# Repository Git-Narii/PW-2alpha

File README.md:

# PW-2alpha
電源基板
PW-2から降圧部分を取り除いた物  
電源用に24V,信号用に5Vを扱う  
12V非対応  
現時点で改良予定

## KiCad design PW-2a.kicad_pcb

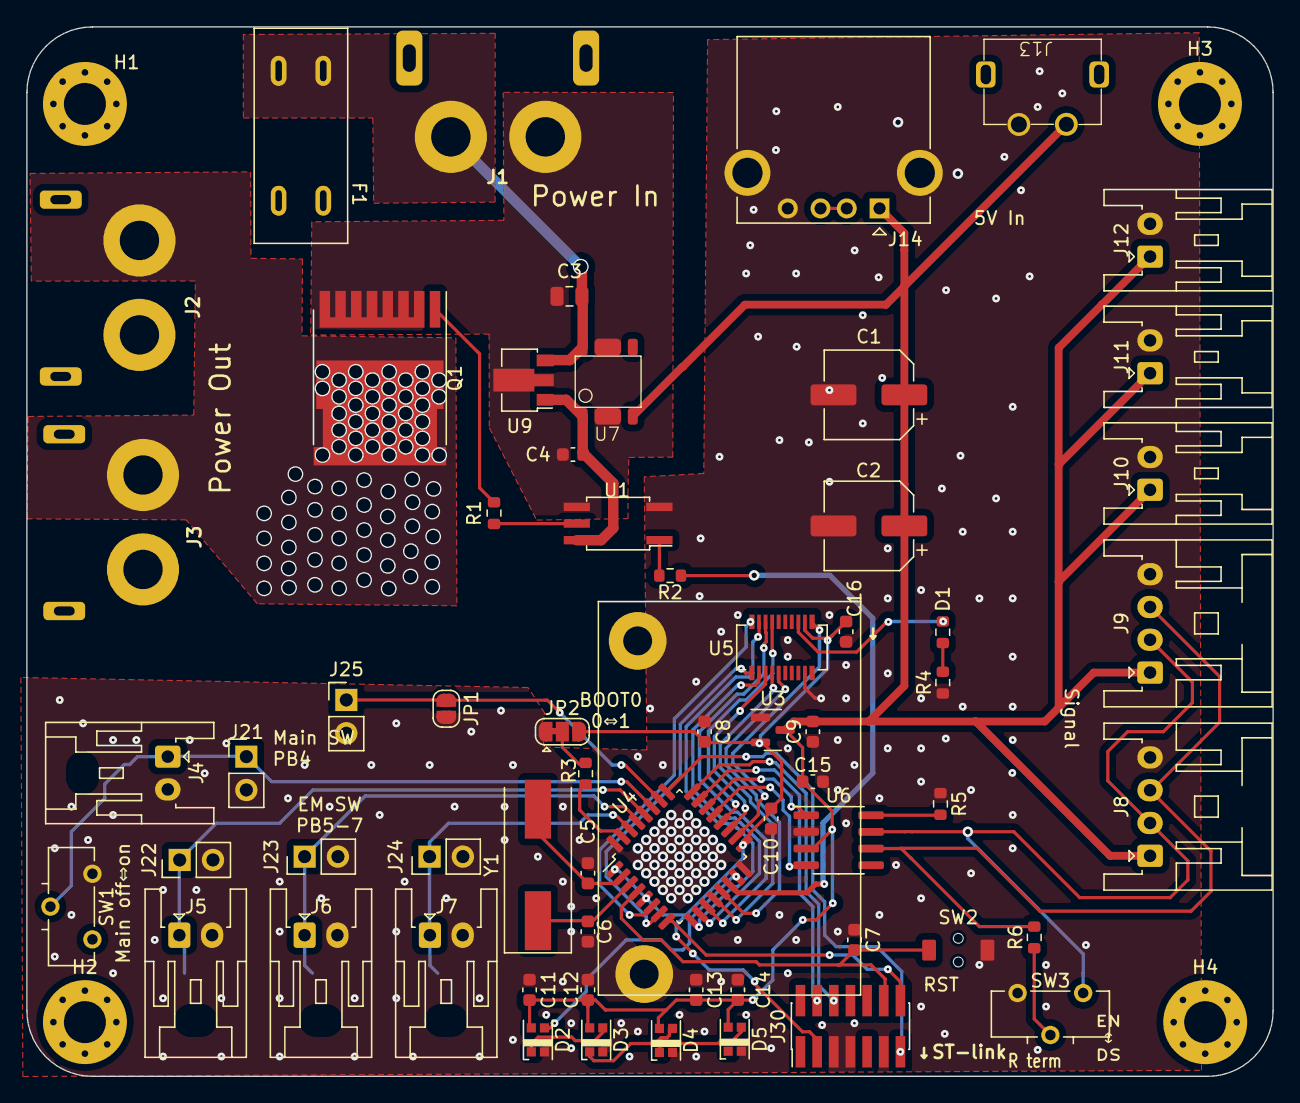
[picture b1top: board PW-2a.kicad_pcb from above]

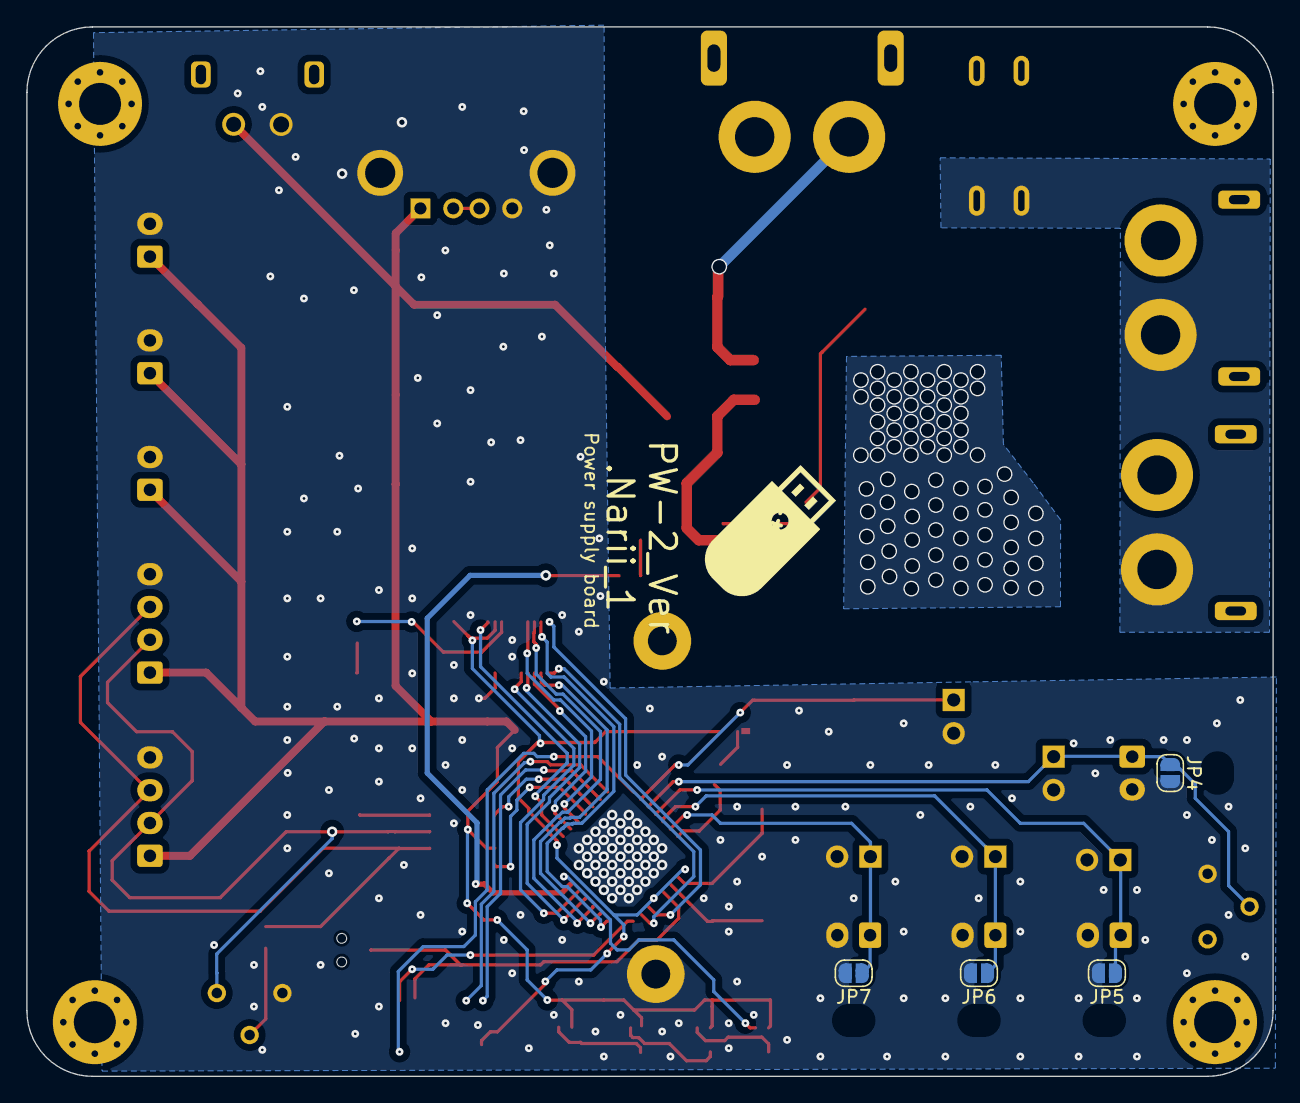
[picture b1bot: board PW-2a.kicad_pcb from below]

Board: 2 copper layers, 95.0 x 80.0 mm, 70 parts (4 on the bottom side), 49 nets.

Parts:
C1, C2: 33u; CP_Elec_6.3x7.7
C3: 330n; C_0805_2012Metric
C4, C7, C10, C11, C12, C13, C14, C15, C16: 100n; C_0603_1608Metric
C5, C6: 22p; C_0603_1608Metric
C8, C9: 1u; C_0603_1608Metric
D1: LED; R_0603_1608Metric
D2, D3, D4, D5: WS2812C; LED_2020Metric_WS2812C_2.0x2.0mm_P1.0mm
F1: Fuse; Fuseholder_Keystone_3568
H1, H2, H3, H4: MountingHole; MountingHole_3.2mm_M3_Pad_Via
J1, J2, J3: XT60
J4, J5, J6, J7, J10, J11, J12: Conn_01x02_Female; JST_XA_S02B-XASK-1_1x02_P2.50mm_Horizontal
J8, J9: Conn_01x04_Female; JST_XA_S04B-XASK-1_1x04_P2.50mm_Horizontal
J13: USB_C PowerOnly
J14: USB_A; USB_A_CONNFLY_DS1095-WNR0
J21, J22, J23, J24, J25: Conn_01x02_Male; PinHeader_1x02_P2.54mm_Vertical
J30: Conn_02x07_Odd_Even; PinHeader_2x07_P1.27mm_Vertical_SMD
JP1, JP4, JP5, JP6, JP7: SolderJumper_2_Open; SolderJumper-2_P1.3mm_Open_RoundedPad1.0x1.5mm
JP2: SolderJumper_3_Bridged12; SolderJumper-3_P1.3mm_Bridged12_RoundedPad1.0x1.5mm
Q1: IPT007N06N; Infineon_PG-HSOF-8-1
R1: 10; R_0603_1608Metric
R2: 330; R_0603_1608Metric
R3, R4, R5: 10k; R_0603_1608Metric
R6: 120; R_0603_1608Metric
SW1, SW3: SW_SPDT; IS-1245T-G
SW2: SW_Push; TVAF06-A020B-R
U1: TLP152; SO-6_5pin_4.4x3.6mm_P1.27mm
U3: MCP1700-3302E_SOT23; SOT-23
U4: STM32F303K8Tx; LQFP-32_7x7mm_P0.8mm
U5: IM920s
U6: MCP2551-I-SN; SOIC-8_3.9x4.9mm_P1.27mm
U7: S-1142DC0l-E6T1U; S-1142DC0I-E6T1U
U9: L78L33_SOT89; SOT-89-3
Y1: 16MHz; Crystal_SMD_HC49-SD

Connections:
+3V3: C8.2, C10.2, C16.2, J30.3, JP2.3 (B), U3.2 (VO), U4.1 (VDD), U4.5 (VDDA), U4.17 (VDD), U5.17 (VCC)
+5V: C1.1, C2.1, C9.2, C11.2, C12.2, C13.2, C14.2, C15.2, D2.4 (VDD), D3.4 (VDD), D4.4 (VDD), D5.4 (VDD), J8.1, J9.1, J10.1, J11.1, J12.1, J13.3 (VBUS), J14.1 (VBUS), U3.3 (VI), U6.3 (VDD), U7.3 (ON/OFF)
+12P: C4.2, U1.6, U7.1 (VOUT), U9.1 (OUT)
+BATT: C3.1, F1.1, J1.2, U7.6 (VIN), U9.3 (IN)
/CANH: J8.2, J9.2, SW3.3 (C), U6.7 (CANH)
/CANL: J8.3, J9.3, R6.2, U6.6 (CANL)
/CAN_RX: U4.21 (PA11), U6.4 (RXD)
/CAN_TX: U4.22 (PA12), U6.1 (TXD)
/IM920_IO1: U4.6 (PA0), U5.1 (IO1/BUSY)
/IM920_IO2: U4.7 (PA1), U5.2 (IO2)
/IM920_IO3: U4.9 (PA3), U5.3 (IO3/XMIT)
/IM920_IO4: U4.10 (PA4), U5.4 (IO4/SLEEP)
/IM920_IO5: U4.11 (PA5), U5.5 (IO5)
/IM920_IO6: U4.19 (PA9), U5.6 (IO6/RxD)
/IM920_IO7: U4.20 (PA10), U5.7 (IO7/TxD)
/IM920_IO8: U4.12 (PA6), U5.8 (IO8)
/IM920_IO10: U4.13 (PA7), U5.10 (IO10)
/IM920_RESET: U4.18 (PA8), U5.19 (RESET)
/NRST: C7.2, J30.12, SW2.2, U4.4 (NRST)
/NeoPixel: D2.3 (DIN), U4.15 (PB1)
/SWCLK: J30.6, U4.24 (PA14)
/SWDIO: J30.4, U4.23 (PA13)
/SW_IN1: J4.1, J21.1, JP4.1 (A), SW1.2 (B), U4.27 (PB4)
/SW_IN2: J5.1, J22.1, JP5.1 (A), U4.28 (PB5)
/SW_IN3: J6.1, J23.1, JP6.1 (A), U4.29 (PB6)
/SW_IN4: J7.1, J24.1, JP7.1 (A), U4.30 (PB7)
/VCP_RX: J30.13, U4.25 (PA15)
/VCP_TX: J30.14, U4.8 (PA2)
/Vout+: F1.2, J2.2, J3.2
/Vout-: J2.1, J3.1, Q1.3 (D)
/breaker_signal: R2.2, U4.14 (PB0)
/disable_remote_kill: J25.1, JP1.1 (A), U4.26 (PB3)
/main_breaker_gate: R1.2, U1.5
GND: C1.2, C2.2, C5.1, C6.1, C7.1, C8.1, C9.1, C10.1, C11.1, C12.1, C13.1, C14.1, C15.1, C16.1, D2.2 (VSS), D3.2 (VSS), D4.2 (VSS), D5.2 (VSS), J4.2, J5.2, J6.2, J7.2, J8.4, J9.4, J10.2, J11.2, J12.2, J13.4 (GND), J14.4 (GND), J14.5 (Shield), J21.2, J22.2, J23.2, J24.2, J25.2, J30.5, J30.7, J30.11, JP1.2 (B), JP2.1 (A), JP4.2 (B), JP5.2 (B), JP6.2 (B), JP7.2 (B), R4.1, R5.1, SW1.1 (A), SW2.1, SW3.1 (A), U1.3, U3.1 (GND), U4.16 (VSS), U4.32 (VSS), U5.18 (GND), U6.2 (VSS)
GNDPWR: C3.2, C4.1, J1.1, Q1.2 (S), U1.4, U7.2 (GND), U7.5 (GND), U9.2 (GND)
unnamed: D1.2 (A), U5.15 (STATUS)
unnamed: D1.1 (K), R4.2
unnamed: D2.1 (DOUT), D3.3 (DIN)
unnamed: D3.1 (DOUT), D4.3 (DIN)
unnamed: D4.1 (DOUT), D5.3 (DIN)
unnamed: J14.2 (D-), J14.3 (D+)
unnamed: JP2.2 (C), R3.1
unnamed: Q1.1 (G), R1.1
unnamed: R2.1, U1.1
unnamed: R6.1, SW3.2 (B)
unnamed: R3.2, U4.31 (BOOT0)
unnamed: C5.2, U4.2 (PF0), Y1.2
unnamed: C6.2, U4.3 (PF1), Y1.1
unnamed: R5.2, U6.8 (Rs)
